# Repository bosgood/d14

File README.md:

# d14

Resources for operating and maintaining the Disorient D14 LED sign.

Read the full manual [here](./docs/d14-manual.pdf).

## Patterns

Find archives of some custom-written Pixelblaze patterns in the [`patterns/`](./patterns) directory.

## Hardware

Find hardware resources like PCB design files in the [`hardware/`](./hardware) directory.

## LED mapping

Find Pixelblaze-compatible LED mapping data in the [`led-mapping/`](./led-mapping) directory.
This data is a JSON array containing the (x, y) coordinates of each LED pixel in 2D space.
It can be copy-pasted into the Mapper tab in the Pixelblaze UI.

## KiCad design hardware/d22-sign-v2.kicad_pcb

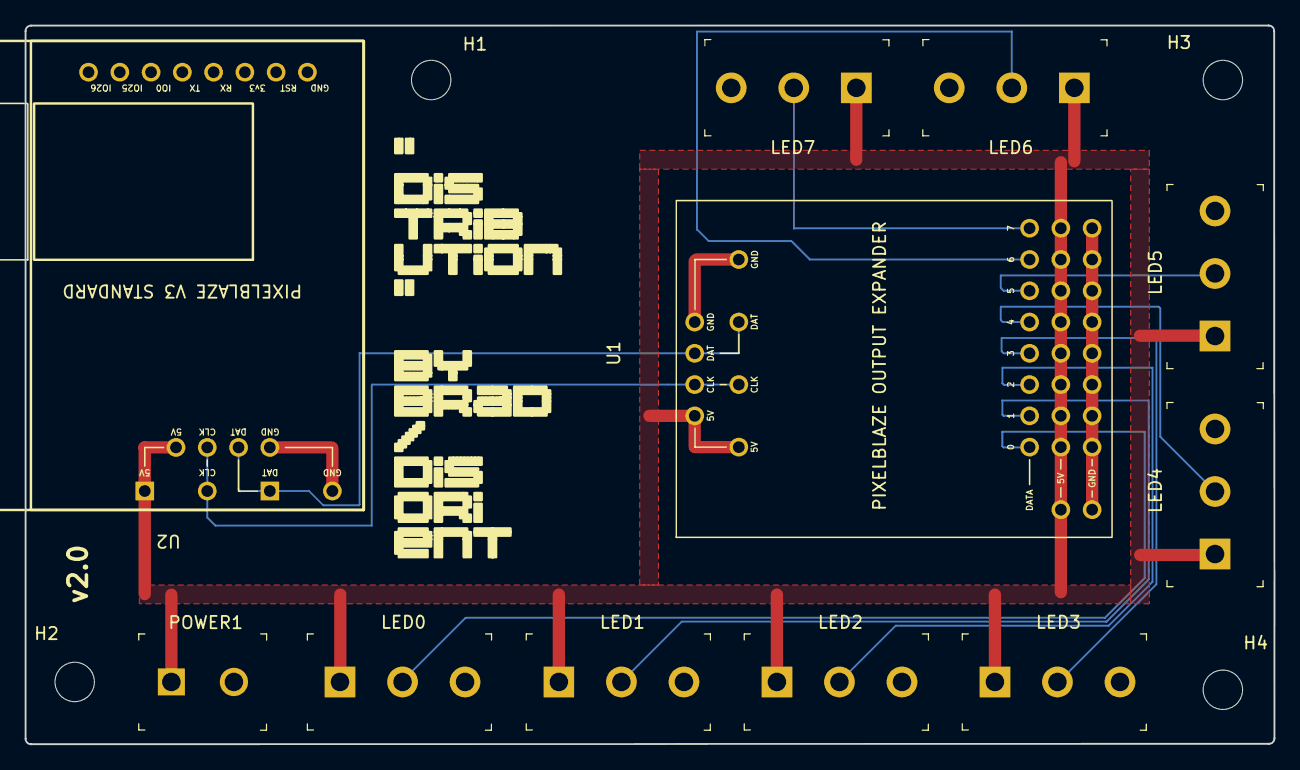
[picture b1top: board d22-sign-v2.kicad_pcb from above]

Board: 2 copper layers, 101.4 x 58.4 mm, 15 parts (0 on the bottom side), 12 nets.

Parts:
H1, H2, H3, H4: MountingHole; MountingHole_3.2mm_M3
LED0, LED1, LED2, LED3, LED4, LED5, LED6, LED7: OSTTC032162; TERM_BLOCK_1x3_P5.08MM
POWER1: OSTTC022162; Term_Block_1x2_P5.08MM
U1: Pixelblaze-Output-Expander
U2: Pixelblaze-V3-Standard

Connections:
+5V: LED0.1, LED1.1, LED2.1, LED3.1, LED4.1, LED5.1, LED6.1, LED7.1, POWER1.1, U1.1 (5V), U1.5 (5V), U1.9 (5V), U1.19 (5V-0), U1.20 (5V-1), U1.21 (5V-2), U1.22 (5V-3), U1.23 (5V-4), U1.24 (5V-5), U1.25 (5V-6), U1.26 (5V-7), U2.4 (5V), U2.8 (5V)
/CLK: U1.2 (CLK), U1.6 (CLK), U2.3 (CLK), U2.7 (CLK)
/D0: LED0.2, U1.11 (D0)
/D1: LED1.2, U1.12 (D1)
/D2: LED2.2, U1.13 (D2)
/D3: LED3.2, U1.14 (D3)
/D4: LED4.2, U1.15 (D4)
/D5: LED5.2, U1.16 (D5)
/D6: LED6.2, U1.17 (D6)
/D7: LED7.2, U1.18 (D7)
/DAT: U1.3 (DAT), U1.7 (DAT), U2.2 (DAT), U2.6 (DAT)
/GND: LED0.3, LED1.3, LED2.3, LED3.3, LED4.3, LED5.3, LED6.3, LED7.3, POWER1.2, U1.4 (GND), U1.8 (GND), U1.10 (GND), U1.27 (G0), U1.28 (G1), U1.29 (G2), U1.30 (G3), U1.31 (G4), U1.32 (G5), U1.33 (G6), U1.34 (G7), U2.1 (GND), U2.5 (GND)

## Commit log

2023-03-05 Add LED mapping readme
2023-03-06 Rename because files are JS not actual PB EPE
2023-03-07 Iterating on D14 docs
2023-03-10 D14 control program discovery
2023-03-10 Leaving TODOs in d14.py
2023-03-20 Fix discover command
2023-03-20 Iterating on command subcommand
2023-04-13 Implement scan and deploy subcommands
2023-04-13 Finalize D14 manual
